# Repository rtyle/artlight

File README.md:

# artlight
This repository supports similar applications that artfully animate light.

Currently, there is a cornhole, wall clock, nixie tube clock and golden clock application supported by this repository.

Golden clock (LED sunflower): https://youtu.be/tHdfZooGRxo

Nixie tube clock: https://youtu.be/5ZdNDDC60QM

Wall clock: https://youtu.be/0ISKXnE9frU

## Parts

### Golden Clock Parts

* [5V 20W power supply](https://www.digikey.com/en/products/detail/cui-inc/SWI25-5-N-P5/7070092)
* [TinyPICO ESP32 development board](https://www.adafruit.com/product/4335)
* SMD 0.1" pin headers for mounting TinyPICO to TinyPICO IO PCB
* 2 position JST PH connection header (bundled in TinyPICO ESP32 development board package) for +5V TinyPICO power
* [3 position JST SH connection header](https://www.digikey.com/en/products/detail/jst-sales-america-inc/SM03B-SRSS-TB(LF)(SN)/926874) for LED SPI signals
* [4 position JST SH connection header](https://www.digikey.com/en/products/detail/sparkfun-electronics/PRT-14417/7652746) for I2C interface with light sensor
* 1024 [SK9822 5050 LEDs](https://www.amazon.com/gp/product/B07QXJSNLN)
* [Barrel connector jack](https://www.digikey.com/product-detail/en/cui-devices/PJ-036AH-SMT-TR/CP-036AHPJCT-ND/1530994) for +5V LED power
* [3 position 0.1" horizontal connection header](https://www.digikey.com/en/products/detail/harwin-inc/M20-8890345/6565716) for LED SPI signals
* [TSL2591 light sensor](https://www.digikey.com/en/products/detail/adafruit-industries-llc/1980/4990786)
* Appropriate cables and connectors for wiring harness
* [12" interior picture frame](https://www.etsy.com/listing/943351523/round-craft-frame-hump-profile-1-14)

### Nixie Tube Clock Parts

* [Bill of Materials](https://github.com/rtyle/artlight/blob/master/easyeda/projects/nixie/bom.csv), plus...
* [AC to 12V DC 1A wall mount power adapter](https://www.digikey.com/product-detail/en/cui-inc/SWI10-12-N-P5/102-4138-ND/6618698)
* 2 [Harwin 15 pin 2.54mm pitch](https://www.mouser.com/ProductDetail/855-M20-8771546) for SMT mount of Huzzah32 board
* 44 [Harwin H3161-05](https://www.digikey.com/product-detail/en/harwin-inc/H3161-05/952-2204-ND/3728169) sockets for nixie tube pins

Optional off-board ambient light sensor for automatic dimming
* [TSL2591 high dynamic range digital light sensor](https://www.adafruit.com/product/1980)
* [SparkFun Qwiic adapter](https://www.sparkfun.com/products/14495) TSL2591 qwiic mount
* 4 [Jumper SSH-003T-P0.2-H X2 12"](https://www.digikey.com/product-detail/en/jst-sales-america-inc/ASSHSSH28K305/455-3077-ND/6009453) TSL2591 qwiic cable
* 2 [Connector housing SH 4pos 1mm white](https://www.digikey.com/product-detail/en/jst-sales-america-inc/SHR-04V-S/455-1394-ND/759883) TSL2591 qwiic connectors

Optional on-board motion sensor plugin module for automatic on/off control
* [PIR detector I2C module](https://www.holtek.com/productdetail/-/vg/7M21x6)
* [Preci-Dip 851-87-006-10-001101 PCB connector](https://www.digikey.com/product-detail/en/preci-dip/851-87-006-10-001101/1212-1350-ND/3757600) PIR I2C mount

Optional base (something is required)
* 1 foot [Cast acrylic tubing 2.000" OD x .250" wall thickness](), cut into 9/16" slices. Four used as pedestals under PCB's nixie tubes.

### Cornhole and Wall Clock Parts

#### Cornhole and Wall Clock Common Parts

* [ESP32 board](https://www.adafruit.com/product/3405)
* [TSL2561 digital luminosity sensor breakout](https://www.adafruit.com/product/439)
* [DotStar digital LED strips](https://www.adafruit.com/product/2241)
* [2.1mm DC barrel jack (through hole)](https://www.adafruit.com/product/373)
* [Wi-Fi range extender (optional)](https://www.amazon.com/gp/product/B072MH1434)

#### Wall Clock Specific Parts

Additional parts for the clock application are
* [40 inch metal wall art](https://www.etsy.com/listing/614388701/round-metal-wall-art-perfect)
* [Custom PCB board for microprocessor](https://github.com/rtyle/artlight/blob/master/eagle/projects/artlight/artlight.brd)
* [Custom PCB board for 12 o'clock ray](https://github.com/rtyle/artlight/blob/master/eagle/projects/ray/ray0.brd)
* [Custom PCB board for other rays](https://github.com/rtyle/artlight/blob/master/eagle/projects/ray/ray.brd)
* [Mounting tape](https://www.amazon.com/gp/product/B00PKI7IBG)
* [Power supply](https://www.adafruit.com/product/1466)
* [Power Y splitter](https://www.amazon.com/gp/product/B06Y5GP7SF)
* [2.1mm DC barrel jack (surface mount)](https://www.sparkfun.com/products/12748)

#### Cornhole Specific Parts

Additional parts for the cornhole application are
* Cornhole board
* [Custom PCB board](https://github.com/rtyle/artlight/blob/master/eagle/projects/artlight/artlight.cornhole.brd)
* [Cornhole LED ring](https://www.amazon.com/gp/product/B01N7SRCQJ)
* [IR break beam sensor](https://www.adafruit.com/product/2168)
* [Vibration sensor](https://www.adafruit.com/product/1766)
* [On/off RGB switch](https://www.adafruit.com/product/3424)
* [Momentary RGB switch](https://www.adafruit.com/product/3423)
* [NPN bipolar transistors](https://www.adafruit.com/product/756)
* [Resistors](https://www.adafruit.com/product/2784)
* [Power bank](https://www.amazon.com/gp/product/B072MH1434)
* [Magnetic mount](https://www.amazon.com/gp/product/B01M0DUVZV)

## Construction

The PCB components were soldered on their respective boards.
When Huzzah32 is powered by USB cable, the 5V power jumper must first be removed.

### Golden Clock Construction

[LED PCB design files](https://github.com/rtyle/artlight/tree/master/easyeda/projects/golden)
and
[TinyPICO IO PCB design files](https://github.com/rtyle/artlight/tree/master/kicad/projects/golden/tinypico-io)

Solder LEDs and connectors to LED PCB.
Solder TinyPICO and connectors to TinyPICO IO PCB.
Build wire harness as necessary for mounting.

### Nixie Tube Clock Construction

[PCB design files](https://github.com/rtyle/artlight/tree/master/easyeda/projects/nixie)

For structural integrity, use a thick (>= 2.0mm) PCB.
Order PCB with a solder paste stencil.
Use the stencil to distribute solder paste for all components under the nixie tubes and solder them with a hot air gun.
Solder all other components individually, as appropriate.
Press in pin sockets and solder from the bottom.
Mount nixie tubes and place PCB on acrylic pedestals.

*WARNING*: The nixie tubes run at 170 volts.
To reduce exposure, do not plug in until tubes are mounted and PCB is placed on acrylic pedestals.

### Wall Clock Construction

[PCB design (artlight.\*) files](https://github.com/rtyle/artlight/tree/master/eagle/projects/artlight)
with
[boards for mounting LED strips on rays](https://github.com/rtyle/artlight/tree/master/eagle/projects/ray)

The microprocessor board is mounted on the back of the art with its luminosity sensor peeking through a hole drilled in the center.
Power is routed and split between the microprocessor and 12 o'clock ray boards.
SPI signals used to animate the individually addressable LEDs are cabled from the microprocessor board to the 12 o'clock board.

LED strips are mounted to the back of the wall art.
To reduce wiring complexity, the 12 rays are supported by PCBs.
12 o'clock is different so there is a special board for it.
Each ray is cut to length, an LED strip is cut to match, mounted with tape and soldered at the ends with LEDs advancing toward the center.
The ray boards are then mounted to the back of the art using more of the same tape.
Small strips are cut to bridge the arcs between ray bases, taped and soldered in place with LEDs advancing clockwise (from front!).
Starting at 12 o'clock, strips are cut and joined together with wire to skirt the perimeter of the art (clockwise, from front).
Only clock and data signals need to tunnel under the rays as 5V and GND can be tapped from the LED strip edges of adjacent rays.

### Cornhole Construction

[PCB design (artlight.cornhole.\*) files](https://github.com/rtyle/artlight/tree/master/eagle/projects/artlight)

The power bank is mounted with strong magnets under the board so that it might easily be unplugged, removed, charged, replaced and plugged back in.
Power from it may be switched on and off (with the on/off switch).
Switched power is split between the microprocessor board, the ring LED strip and the high side of the RGB LEDs in all the switches.

The R, G and B LEDs in the switches are separtely pulse-width-modulated (PWM) to mix the preferred color of each.
PWM switching is controlled indirectly through transistor circuits wired to the low side of the RGB LEDs of each switch.
The momentary switch outputs (closed to ground) are wired to the microprocessor board inputs dedicated for them.

Vibration sensors are strategically placed (for best performance) under the board.
The vibration sensor part may be changed to affect its sensitivity.
Their shared (parallel) output (closed to ground) is wired to the microprocessor board input dedicated for them.

IR break beam sensors are mounted across the cornhole ring for the best coverage (2 orthogonal pairs seems adequate).
Their shared (parallel) output (closed to ground) is wired to the microprocessor board input dedicated for them.

The LEDs that come with the cornhole LED ring are replaced with a clockwise (from the top) strip of 80 individually addressable LEDs.
Their control lines are wired to the microprocessor board output dedicated for them.
The ring is mounted under the board.
For best results, the material above the LED ring should be transparent (for example, an acrylic ring)
so that the lights under the board can be seen from above.

## Use

Applications must be provisioned on a Wi-Fi LAN.
Until this is done, they will offer their own Wi-Fi access point where they can be configured securely by a web browser (https://192.168.4.1).
The SSID and password for Wi-Fi access must be entered.
Optionally, an mDNS hostname may be given.

The reach of your Wi-Fi LAN may need to be increased to reach these devices.
This is best done by repositioning the devices and/or Wi-Fi access points.
If necessary, deploy a Wi-Fi range extender.

Once provisioned, preferences may be set for each application by pointing a web browser to the device (http://\<device\>/).
If supported, the mDNS hostname may be used to resolve the device address;
otherwise, the leased IP address will have to be resolved (perhaps manually) depending on the capabilities of the LAN's DHCP/DNS services.

The preferences page may be filled using "factory" default values or with the current values.
Changes to most will take effect immediately.
If not, then they will take effect when the form is submitted.

Preferences may be used to customize the presentation.
Brightness parameters may be set which may include use of the luminosity sensor.
The mDNS hostname of the board may be changed.
Parameters may be set in order to accurately present time in the given time zone.
Over-the-air software updates may also be performed.

## Golden Clock Use

It's "golden" because the LED layout that produces the spirals is based on the [golden ratio](https://en.wikipedia.org/wiki/Golden_ratio).

In clock mode, the length, width, curl, shape and color of each hand may be customized. During the first minute of each hour, the minute and second hands are suppressed and the hour hand is etched into a matching randomized swirling pattern.

In swirl mode, the randomized swirling pattern cycles through six different minute-long phases, each aligned to a particular set of spirals.

The number of spirals in each set are [Fibonacci numbers](https://en.wikipedia.org/wiki/Fibonacci_number) (13, 21, 34, 55, 89, 144).
The lower the number, the tighter (curlier) the spirals in the set.
Of all the Fibonacci numbers, these ones resolve best on a layout with this number of LEDs.
By default, the sets with 21, 55 and 144 spirals are used to resolve the hour, minute and second hands because they all curve the same way and most all are sufficient to resolve the units of their measure.
Unfortunately, 55 is not quite enough resolution for 60 minutes but it looks better than the spiral set of 89 because that curves the other way.
In any case, you can choose what you like.

A high quality power supply is required to power both the microcontroller and the LEDs.
It may be necessary to use separate power supplies for these.
If so, they must tolerate having their grounds tied together.

## Nixie Tube Clock Use

The bottom dot of the colon pulses at 30 beats per minute (a second on and a second off).
The top dot of the colon pulses at 31 beats per minute.
This results in pulsing dots that are in phase at the beginning of the minute.
They separate more as mid-minute is approached and come back together again as the next minute is approached.
Thus the colon is a very crude seconds display.

Dimming controls should be slid all the way to the left to disable dimming; otherwise, dimming will start to occur as it gets dark.
The further to the right the dimming control is set, the more dimming will be done.
When slid all the way to the right, the controlled element will dim to black when the room is black.

In an effort to combat [nixie tube cathode poisoning](https://www.google.com/search?q=nixie+tube+cathode+poisoning)
the clock will not display minutes during the first minute of every hour.
Instead, the normal minutes-places will cycle through digits that are not normally used there.
For hours less than 10, the tens-of-hours place will similarly cycle.
The display can also be temporarily put in a Clean mode (or other modes) until expectations are met.

## Wall Clock Use

There are no additional preferences for the clock application.

The clock will present time by animating hour, minute and second indicators using the LEDs mounted to the back of the art.
Hour and minute indicators will animate up and down the rays and across the inner arcs that connect them.
The second indicator will sweep across the perimeter.

## Cornhole Use

The cornhole "preferences" page may be used to keep score.
In fact, unless explicitly accessed through a URL with a preferences path (http://\<device\>/preferences), scoring is the only thing allowed.

Changing most preferences (including scoring) will be shared between boards that have been configured to use the same network port number.
For this to work effectively, only the two boards used in a cornhole game should share the same port number and each must be reachable from the other on the same network.

A preference may be used to control what the ring LED strip indicates:
* The score of each team
* The time
* Various animations

Regardless of what the ring indicates:

A short press of a momentary switch will increment the score of the associated team.
A long press of a momentary switch will decrement the score of the associated team while held.
While decrementing, if the other switch is down too then the score is reset to 0 (hold both to reset both to 0).

Vibration from the board will cause a short "lightning strike" animation to be presented over the existing ring indication.
A break in the ring's IR beam sensors will cause a short "fireworks" animation to be presented over the existing ring indication.

## Software Build, Deploy and Monitor

These projects were built on a Fedora Linux platform.
Your mileage may vary elsewhere.

Get artlight source code with its dependencies

    git clone http://github.com/rtyle/artlight.git
    cd artlight
    git submodule update --init --recursive
    (cd esp-idf; git apply ../time.c.patch)
  
[Create certificates](https://github.com/rtyle/artlight/blob/master/project/README.certificates.txt)

Install tools required by esp-idf in esp-idf-tools.

    IDF_TOOLS_PATH=esp-idf-tools esp-idf/install.sh

(Re)establish build environment.

    . esp-idf-export.sh

Select application (choose one).

    application=clock
    application=cornhole
    application=golden
    application=nixie

Build application.

    (cd project; ArtlightApplication=$application idf.py fullclean reconfigure build)

Grant user access to USB serial devices then **relogin** to get access.

    sudo usermod -a -G dialout $USER

Identify serial port to connected device.
For example,

    port=/dev/ttyUSB0

Prepare connected device and deploy application.

    (cd project; idf.py -p $port erase_flash erase_otadata)
    (cd project; idf.py -p $port flash)

Monitor serial output from device.

    (cd project; idf.py -p $port monitor)

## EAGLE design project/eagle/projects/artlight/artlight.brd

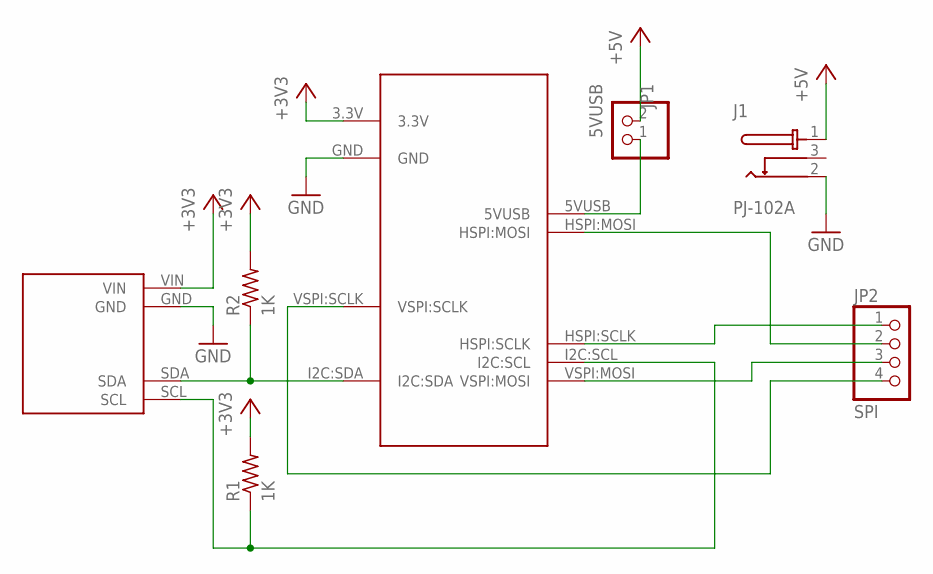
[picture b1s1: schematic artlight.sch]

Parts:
J1: PJ-102A; CUI_PJ-102A
JP1: 5VUSB; 1X02/90
JP2: SPI; 1X04/90
R1, R2: 1K; 0204/7
U$1: HUZZAH32-ARTLIGHT; FEATHERWING-ARTLIGHT
U$3: TSL2561-ARTLIGHT

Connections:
3: J1.3
5VUSB: JP1.1, U$1.5VUSB
+3V3: R1.2, R2.2, U$1.3.3V, U$3.VIN
+5V: J1.1, JP1.2
GND: J1.2, U$1.GND, U$3.GND
HSPI-MOSI: JP2.2, U$1.HSPI:MOSI
I2C-SCL: R1.1, U$1.I2C:SCL, U$3.SCL
I2C-SDA: R2.1, U$1.I2C:SDA, U$3.SDA
unnamed: JP2.3, U$1.VSPI:MOSI
unnamed: JP2.1, U$1.HSPI:SCLK
VSPI-SCLK: JP2.4, U$1.VSPI:SCLK

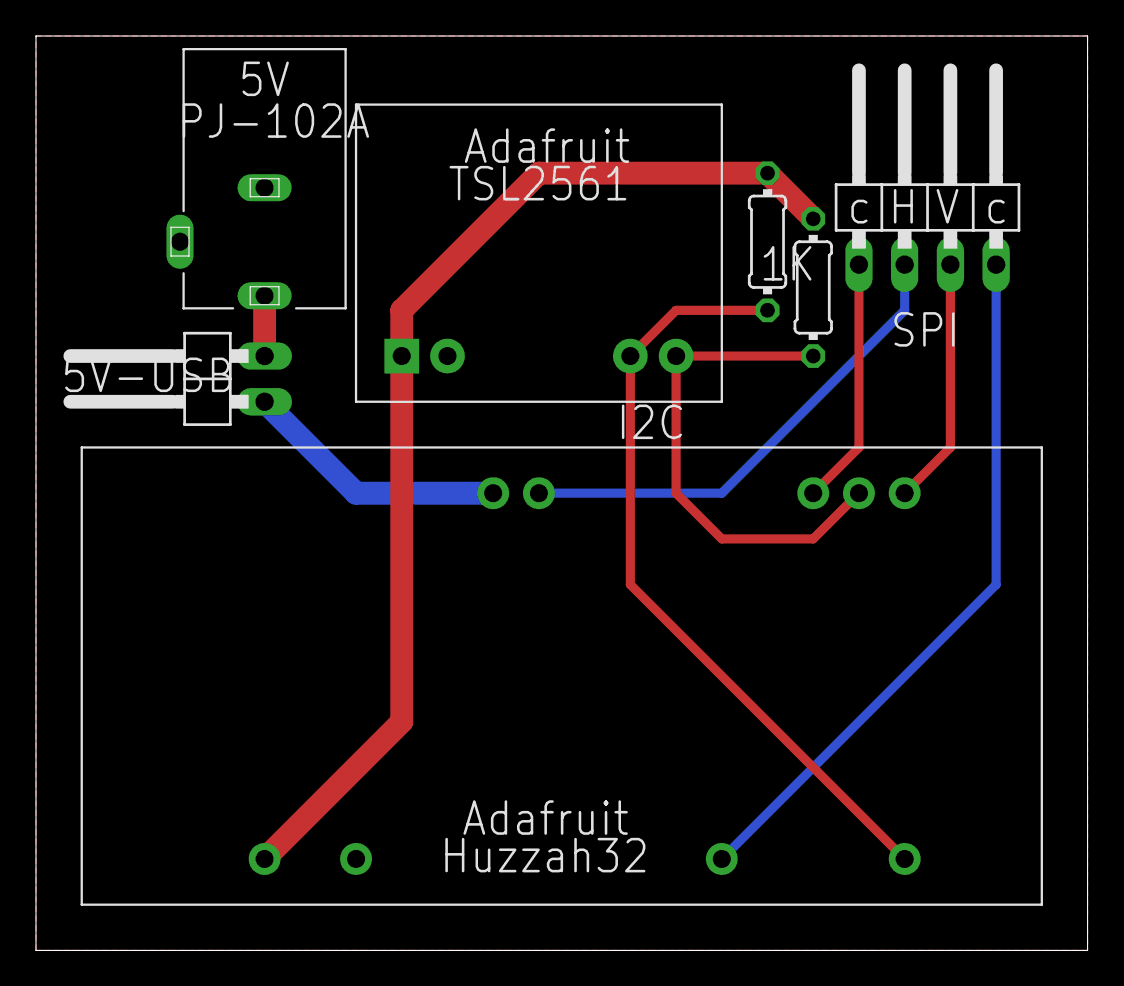
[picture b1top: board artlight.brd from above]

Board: 2 copper layers, 58.4 x 50.8 mm, 7 parts (0 on the bottom side), 10 nets.

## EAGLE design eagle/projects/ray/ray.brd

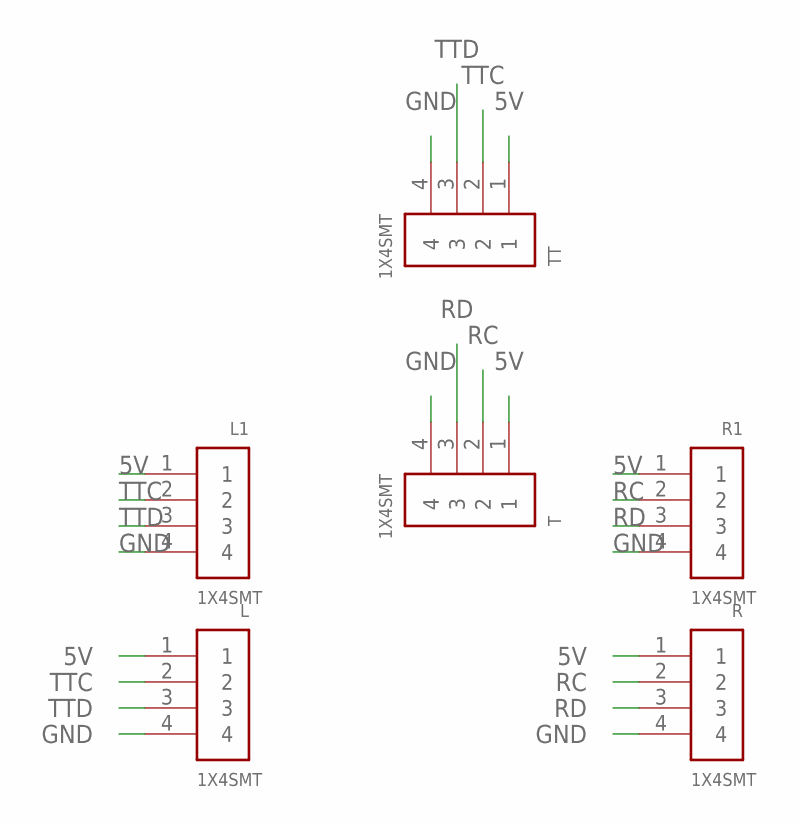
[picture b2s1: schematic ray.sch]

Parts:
L, L1: 1X4SMT; 1X4-SMT
R, R1: 1X4SMT; 1X4-SMT
T: 1X4SMT; 1X4-SMT
TT: 1X4SMT; 1X4-SMT

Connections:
5V: L.1, L1.1, R.1, R1.1, T.1, TT.1
GND: L.4, L1.4, R.4, R1.4, T.4, TT.4
RC: R.2, R1.2, T.2
RD: R.3, R1.3, T.3
TTC: L.2, L1.2, TT.2
TTD: L.3, L1.3, TT.3

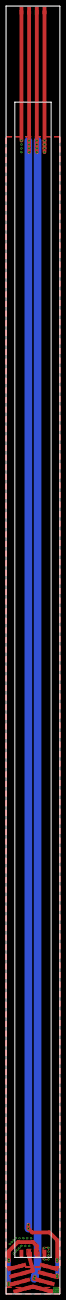
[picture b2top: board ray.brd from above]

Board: 2 copper layers, 17.8 x 425.4 mm, 6 parts (0 on the bottom side), 6 nets.

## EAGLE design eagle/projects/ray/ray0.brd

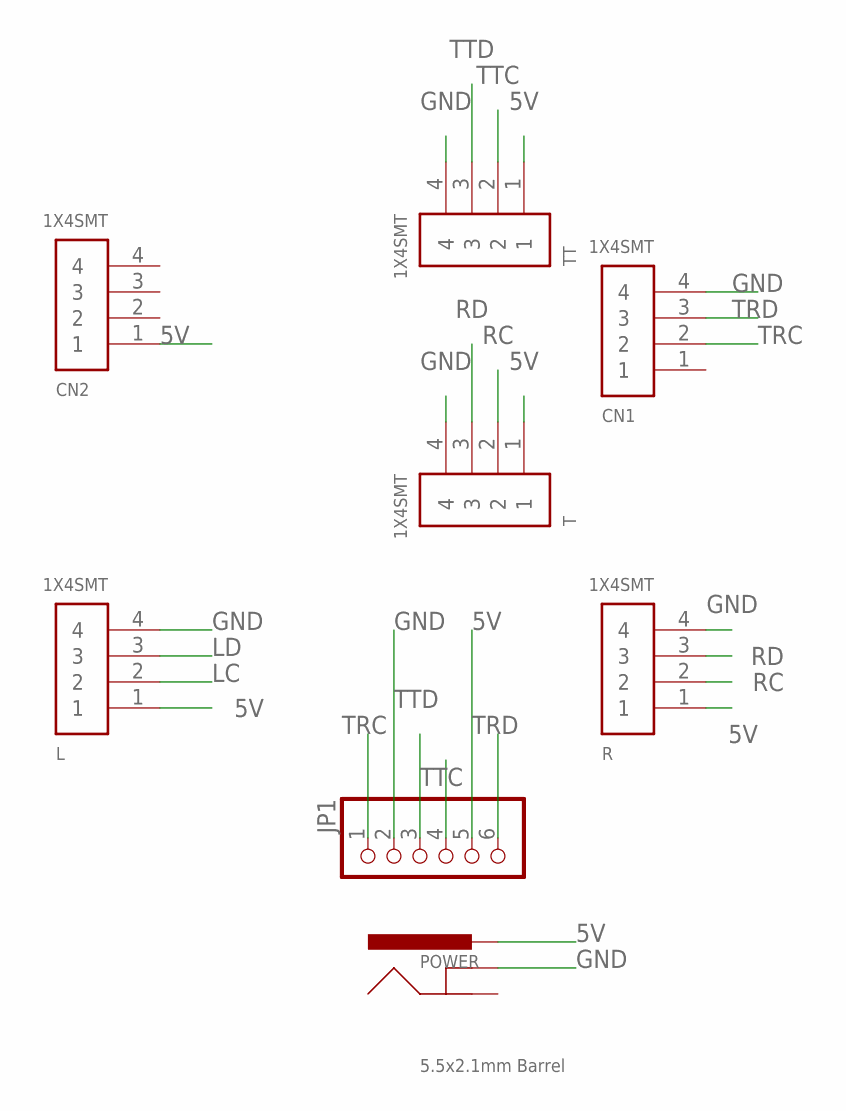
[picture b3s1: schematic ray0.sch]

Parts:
CN1, CN2: 1X4SMT; 1X4-SMT
JP1: PINHD-1X6; 1X06
L: 1X4SMT; 1X4-SMT
POWER: 5.5x2.1mm Barrel; POWER_JACK_SMD
R: 1X4SMT; 1X4-SMT
T: 1X4SMT; 1X4-SMT
TT: 1X4SMT; 1X4-SMT

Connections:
5V: CN2.1, JP1.5, L.1, POWER.VIN0 (PWR), POWER.VIN1 (PWR), R.1, T.1, TT.1
GND: CN1.4, JP1.2, L.4, POWER.GND (GNDBREAK), R.4, T.4, TT.4
LC: L.2
LD: L.3
RC: R.2, T.2
RD: R.3, T.3
TRC: CN1.2, JP1.1
TRD: CN1.3, JP1.6
TTC: JP1.4, TT.2
TTD: JP1.3, TT.3

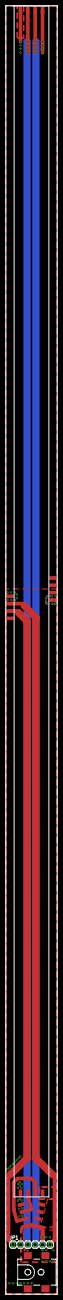
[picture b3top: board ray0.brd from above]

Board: 2 copper layers, 17.8 x 445.5 mm, 8 parts (0 on the bottom side), 8 nets.

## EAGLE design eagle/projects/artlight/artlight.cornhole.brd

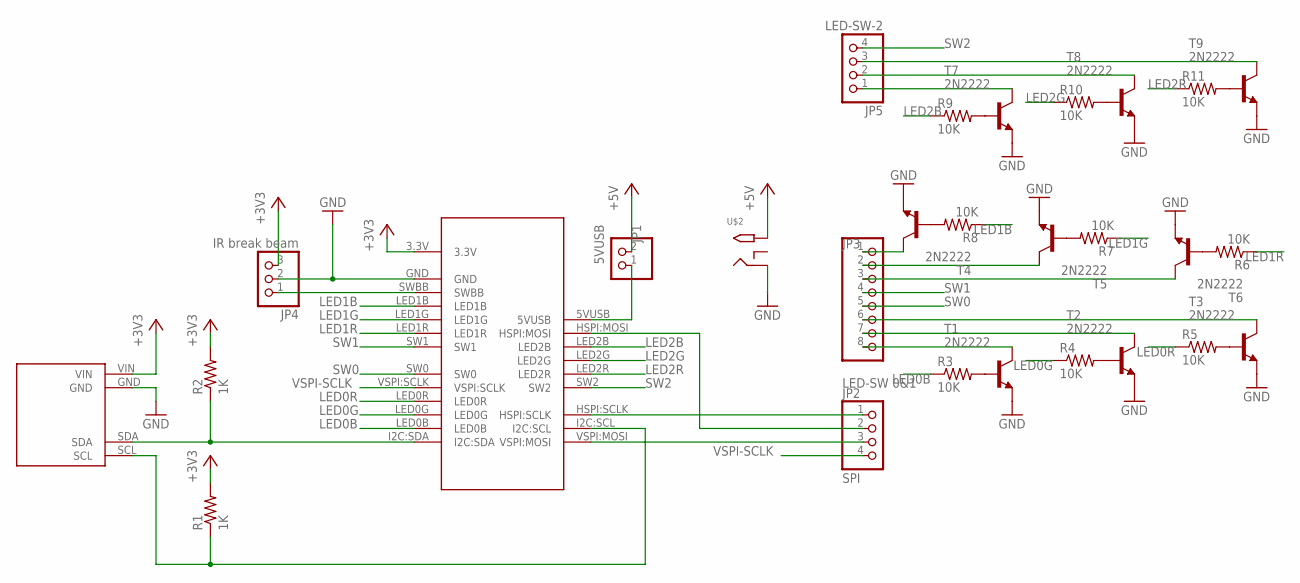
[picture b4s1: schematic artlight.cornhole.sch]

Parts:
JP1: 5VUSB; 1X02
JP2: SPI; 1X04
JP3: LED-SW 0&1; 1X08
JP4: IR break beam; 1X03
JP5: LED-SW-2; 1X04
R1, R2: 1K; 0204/7
R3, R4, R5, R6, R7, R8, R9, R10, R11: 10K; 0204V
T1, T2, T3, T4, T5, T6, T7, T8, T9: 2N2222; TO92-EBC-OVAL
U$1: HUZZAH32-ARTLIGHT.CORNHOLE; FEATHERWING-ARTLIGHT.CORNHOLE
U$2: 2.1MMJACKTHM; PJ-102A
U$3: TSL2561-ARTLIGHT

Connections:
5VUSB: JP1.1, U$1.5VUSB
+3V3: JP4.3, R1.2, R2.2, U$1.3.3V, U$3.VIN
+5V: JP1.2, U$2.TIP
GND: JP4.2, T1.E, T2.E, T3.E, T4.E, T5.E, T6.E, T7.E, T8.E, T9.E, U$1.GND, U$2.RING, U$3.GND
HSPI-MOSI: JP2.2, U$1.HSPI:MOSI
HSPI-SCLK: JP2.1, U$1.HSPI:SCLK
I2C-SCL: R1.1, U$1.I2C:SCL, U$3.SCL
I2C-SDA: R2.1, U$1.I2C:SDA, U$3.SDA
LED0B: R3.1, U$1.LED0B
LED0B-BASE: R3.2, T1.B
LED0B-PIN: JP3.8, T1.C
LED0G: R4.1, U$1.LED0G
LED0G-BASE: R4.2, T2.B
LED0G-PIN: JP3.7, T2.C
LED0R: R5.1, U$1.LED0R
LED0R-BASE: R5.2, T3.B
LED0R-PIN: JP3.6, T3.C
LED1B: R8.1, U$1.LED1B
LED1B-BASE: R8.2, T4.B
LED1B-PIN: JP3.1, T4.C
LED1G: R7.1, U$1.LED1G
LED1G-BASE: R7.2, T5.B
LED1G-PIN: JP3.2, T5.C
LED1R: R6.1, U$1.LED1R
LED1R-BASE: R6.2, T6.B
LED1R-PIN: JP3.3, T6.C
LED2B: R9.1, U$1.LED2B
LED2B-BASE: R9.2, T7.B
LED2B-PIN: JP5.1, T7.C
LED2G: R10.1, U$1.LED2G
LED2G-BASE: R10.2, T8.B
LED2G-PIN: JP5.2, T8.C
LED2R: R11.1, U$1.LED2R
LED2R-BASE: R11.2, T9.B
LED2R-PIN: JP5.3, T9.C
SW0: JP3.5, U$1.SW0
SW1: JP3.4, U$1.SW1
SW2: JP5.4, U$1.SW2
SWBB: JP4.1, U$1.SWBB
VSPI-MOSI: JP2.3, U$1.VSPI:MOSI
VSPI-SCLK: JP2.4, U$1.VSPI:SCLK

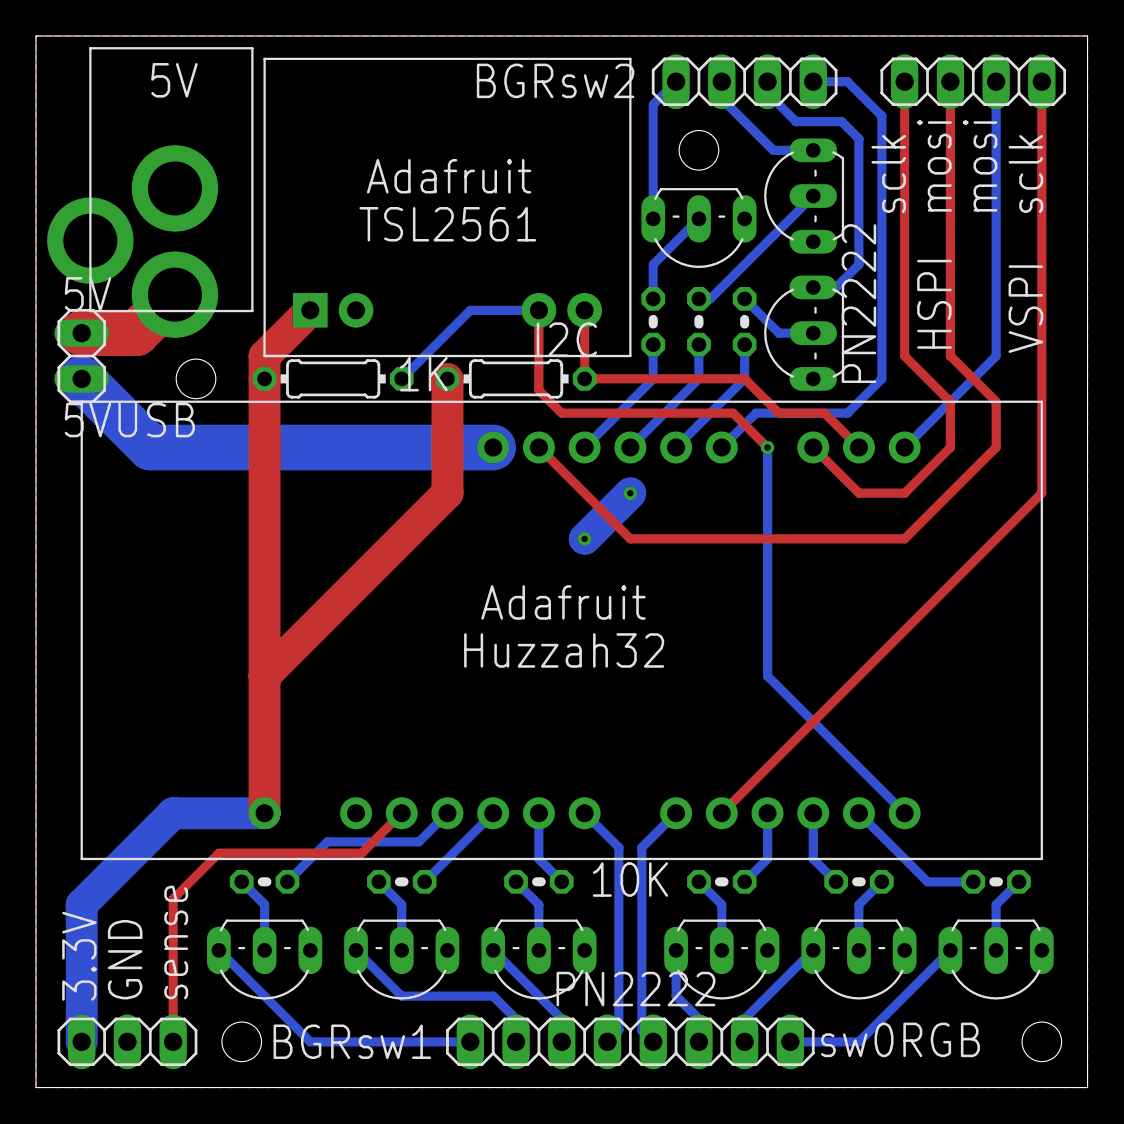
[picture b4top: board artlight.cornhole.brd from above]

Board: 2 copper layers, 58.4 x 58.4 mm, 28 parts (0 on the bottom side), 41 nets.

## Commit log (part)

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2019-02-28 move Pin observation and LED handling into Ring
2019-02-28 fix LEDC timer and channel allocation
2019-02-28 animage a and b buttons
2019-03-01 refactor
2019-03-01 led pulse with different relatively irrational frequencies
2019-03-01 refactor, comment
2019-03-02 rename
2019-03-05 Button
2019-03-07 refactor: rename
2019-03-07 Button refactor, rename, comment, tune
2019-03-08 APA102.cpp: fix toString conversion
2019-03-08 ArtTask.fadesObserver sets a ceiling on fades
2019-03-08 BellWave fixes
2019-03-09 whitespace
2019-03-09 comment
2019-03-11 preferences: {a,b,c}Shape select
2019-03-11 all ArtTask enumerated preferences handled the same way
2019-03-12 preferences: use HTML select instead of radio
2019-03-13 remove unused function.h
2019-03-13 refactor out most Ring content, place what is left in CornholeArtTask
2019-03-14 preferences: cornhole score
2019-03-14 automatically POST input numbers
2019-03-14 observe/update cornhole score
2019-03-17 emit Button held when released after hold
2019-03-17 CornholeArtTask increment/decrement score
2019-03-18 remove {a,b,c}Fades preferences - default to black
2019-03-19 display cornhole winner only
2019-03-19 for cornhole, hide all preferences except score if pathname is /
2019-03-19 fix compiler warnings
2019-03-19 optionally provision with mDNS hostname to override default/preference
2019-03-19 implement mDNS hostname preference
2019-03-20 fix ESP_ERR_NVS_NOT_FOUND error handling
2019-03-21 KeyValueBroker: support RemoteObserver(s)
2019-03-22 PeerTask sends and receives key/values to/from peers
2019-03-22 PeerTask cleanup
2019-03-22 add semi-colon line terminator after ESP_ERROR_CHECK macro
2019-03-22 esp-idf v3.2-beta3
2019-03-23 document lwip_recvmsg bug
2019-03-23 KeyValueBroker: remote -> general, publish takes fromPeer bool
2019-03-23 Cornhole::scoreObserved ignores values greater than scoreMax
2019-03-23 fix input validity check
2019-03-23 ArtTask::widthObserved: add validity check
2019-03-24 ArtTask validate dimLevel and gamma
2019-03-24 validate mDNS hostname
2019-03-24 use jquery-knob for cornhole score
2019-03-25 dynamically change {a,b}Score bgColor to {a,b}Color
2019-03-25 {a,b}Score 800x800
2019-03-25 spectrum.js
2019-03-25 remove color pattern, terminate input xml elements
2019-03-25 input type='text' class='spectrum'
2019-03-25 spectrum input elements are not just for cornhole
2019-03-26 fix knob release POST
2019-03-26 preferences.html.m4 changequote to «»
2019-03-28 preferences: make otaStart a button that submits otaUrl and starts OTA
2019-03-28 preferences: don't mess with button labels
2019-04-01 fix allocation bugs in LEDC.cpp
2019-04-02 WebSocketTask
2019-04-02 WebSocketTask close session on protocol error
2019-04-02 WebSocket::acceptSession should std::forward socket instead of std::move it
2019-04-02 KeyValueBroker::serialize(key, value)
2019-04-02 WebSocketTask sprays key value changes
2019-04-02 CONFIG_LWIP_MAX_SOCKETS=16
2019-04-04 maximize ota app partition sizes
2019-04-04 WebSocketTask: use std::move instead of std::forward, comment on shared_ptr usage
2019-04-11 Button held(int)
2019-04-11 Dial.* -> Curve.*, add lighting strikes after hole event
2019-04-12 tune lightning
2019-04-13 Bloom shape
2019-04-17 BumpCurve -> BumpsCurve
2019-04-17 BumpCurve
2019-04-17 CONFIG_TIMER_TASK_STACK_DEPTH=4096
2019-04-17 add/tune Bloom use
2019-04-17 tune Bloom
2019-04-19 https://raw.githubusercontent.com/Reputeless/PerlinNoise/master/PerlinNoise.hpp
2019-04-19 remove siv namespace from PerlinNoise
2019-04-19 PerlinNoise: double -> float
2019-04-19 mode: noise
2019-04-20 tune Perlin noise
2019-04-26 Sawtooth -> SawtoothCurve
2019-05-03 bell width is 4 sigma. calculate phase in time accurately for large time
2019-05-05 remove need for explicit PerlinNoise construction
2019-05-05 tune CornholeArtTask Spin mode
2019-05-06 CornholeArtTask Spin mode: fix wave position drift with time and changing width
2019-05-06 cleanup
2019-05-06 CornholeArtTask: pulse hour, minute and second hands on clock
2019-05-15 label auto-generated date in preferences.html as 'Version:'
2019-06-02 swap A and B (switch and LEDs)
2019-08-20 triggering a change event on a knob also triggers a release event, processing of which must be inhibited
2020-02-16 fix FoldsInRing to handle uneven folds
2020-02-17 README.md
2020-02-19 ArtLightClock.h, ClockArtTask.{h,cpp}
2020-02-19 add clock to suite of ArtLightApplication
2020-02-19 mode preference for all but score only for cornhole
2020-02-20 fix message to handle both APA102 and clone (SK9822)
2020-02-22 catch update rate too fast
2020-02-25 expose smoothTimeStepCount arg (with default and ClockArtTask override) in ArtTask constructor
2020-02-25 ClockArtTask renders to two rings: one for hours and minutes, the other for seconds
2020-03-10 add reverse checkbox input to clock preferences
2020-03-17 adjust ringSize & foldedSize to match art
2020-03-23 esp-idf v3.3.1
2020-03-29 README.md youtube link
2020-03-31 increase max indicator width from 16 to 64
2020-04-01 dialCount, ringCount, sectorCount constexpr
2020-04-01 CPP core guidelines ES.23: Prefer {} -initializer syntax
2020-04-01 sum constexpr
2020-04-02 static methods
2020-04-02 align with esp-idf v3.3.1 components/newlib/time.c
2020-04-02 fix broken time after OTA update
2020-04-28 factor out LED dial stuff from ArtTask into DialArtTask from which both ClockArtTask and CornholeArtTask now derive from
2020-04-28 ArtLightNixie skeleton
2020-05-01 TLC59711 LED driver SPI interface
2020-05-06 move SPI and I2C setup to {Clock,Cornhole,Nixie}ArtTask constructors
2020-05-17 inSecondOf not used
2020-05-17 I2C writeBytes takes const data
2020-05-17 ignoreKnobRelease only for cornhole
2020-05-24 LuxTask uses abstract LuxSensor implementation
2020-05-25 LuxSensor implementations keep track of startTime to detect underflow
2020-05-26 TSL25xx overflow only when too sensitive, underflow when not sensitive enough
2020-05-29 remove startTime from TSL2591. disable debug in TSL2561
2020-05-30 TSL2591 readLux behaves like TSL2561 until we know better
2020-05-30 add another tick to LuxTask soonAfterAvailable to eliminate occasional TSL2591 underflows
2020-06-02 LuxTask -> SensorTask, a shell task for synchronizing access to sensors
2020-06-06 incorporate TSL2591 lux equation guidance from AMS
2020-06-09 easyeda
2020-06-09 nixie clock
2020-06-10 do not repeat yourself
2020-06-12 luxBrightest
2020-07-24 add roll mode. map to nixie digits. blink colon. turn on LEDs
2020-07-25 use float powf
2020-07-25 default dots function returns 0. digitize{0,1} never returns more than 1. do not display hours 10 digit if 0. enforce minimum pwm
2020-07-25 create and use a simple PCA9685:Pwm operator that modifies itself using one unsigned value
2020-07-25 snapPwm to 0 if less than minimum value
2020-07-25 pwmFactorOf(digit)
2020-07-26 add manual clean mode and automatically clean in clock mode every hour
2020-07-27 constexpr pwmFactorFrom
2020-07-27 make sure an LED level of 1 does not turn the LED off
2020-07-27 linear dimming as a function of ambient lighting and preferences
2020-07-28 nixie dimming before brightness, no separate brightness section
2020-07-28 set nixie dimming step to 4, fade colon dots
2020-07-29 characterize nixie tube brightness in our circuit
2020-07-30 maximum LED dimming (off when pitch black) as default
2020-07-30 add nixie tube clock
2020-07-30 170 volt warning
2020-07-31 make TSL2591 I2C device optional
2020-07-31 mark optional nixie tube clock parts
2020-07-31 punctuation
2020-08-01 README links to PCB design files
2020-08-01 add Software Build, Deploy and Monitor section to README.md
2020-08-02 nixie clock motion sensor is optional. default preference update
2020-08-06 APA102::Message constructor creates encodings from default LED constructor
2020-08-06 LuxSensor::update catches all exceptions
2020-08-06 motion tooltips
2020-08-07 {initialization}
2020-08-08 set I2C clock for nixie sensor bus to 400000 (fast mode)
2020-08-10 esp_err_to_name
2020-08-11 HT7M2xxx rework
2020-08-13 avoid throw during catch
2020-08-13 Finally processing in I2C::Master::Commands desttuctor
2020-08-15 {Time,Dial,Light}Preferences
2020-08-15 pirRetrigger_(true)
2020-08-16 unneeded
2020-08-20 ESP-IDF v3.3.2, latest xtensa toolchain
2020-08-20 I2C::Master::Commands destructor checks for successful construction
2020-08-21 move sensorTask.start() to NixieArtTask::run()
2020-08-21 MotionSensor::getPeriod returns ticks
2020-08-22 not needed
2020-09-13 org.eclipse.cdt.core
2020-09-13 increase effectiveness of cathode poisoning prevention routine
2020-09-13 microsecondsSinceBootOfModeChange = get_time_since_boot()
2020-09-13 distinguish betwee decimal place index and values
2020-12-13 Pin.h disable pullups by default
2020-12-17 golden application stub on TinyPICO
2020-12-19 EasyEDA golden schematic and PCB artifacts
2020-12-19 golden.html
2020-12-20 calculate the positioning and ordering LEDs in the spiral "strip"
2020-12-30 golden.html: add parameters and links for good pre-defined combinations
2021-01-20 golden.html: numbers for c++ code
2021-01-21 GoldenArtTask: swirl
2021-01-21 GoldenArtTask: fibonacci, narrow scope
2021-01-22 GoldenArtTask: add contrast
2021-01-22 GoldenArtTask: better compile-time initialization
2021-01-23 GoldenArtTask: apply noise to radius, stretch noise with contrast
2021-01-24 GoldenArtTask: cycle through even then odd swirls
2021-01-24 GoldedArtTask: modes
2021-01-25 GoldenArtTask: Path::Iterator
2021-01-26 GoldenArtTask: clock
2021-01-26 GoldenArtTask: dim clock
2021-01-26 HalfDial
2021-01-27 HalfDial -> HalfCurve
2021-01-27 GoldenArtTask: no pulse, no scale, half indicator by direction
2021-01-28 GoldenArtTask: rename for fibonacci index
2021-01-30 SawtoothCurve::operator(): handle negative values from std::modf properly
2021-01-31 GoldenArtTask: struct Rim
2021-01-31 GoldenArtTask: index -> fibonacciIndex
2021-01-31 GoldenArtTask: rimEnd, rimName, rimDecl macros
2021-01-31 GoldenArtTask: wavePhase same for all dials, fix seam, break period for secondsDial
2021-02-01 GoldenArtTask: adjust wavePosition only for odd rimSizes
2021-02-01 GoldenArtTask: dial edge always full on
2021-02-01 GoldenArtTask: better name, reduce scope
2021-02-03 golden.html: tune rims
2021-02-03 GoldenArtTask: swirls based only on needed rims in cycle, get rid of rest
2021-02-03 golden.html: fix inconsistencies
2021-02-03 GoldenArtTask: change rim[] common_type to Array<Rim const>
2021-02-04 Array.h
2021-02-04 Update Array.h
    comment
2021-02-04 golden: add curl and length preferences
2021-02-05 GoldenArtTask: normalize width
2021-02-06 GoldenArtTask: compose rendering with int16_t precision, apply gamma correction, then encode
2021-02-06 golden brightness preference UI
2021-02-06 reduce scope
2021-02-06 GoldenArtTask: comment, name constants
2021-02-06 golden: add lux sensor with brightness/dimming controls
2021-02-07 GoldenArtTask: do not gamma correct zero
2021-02-07 golden: make sure color dimming & gamma correction do not lose non-zero rgb parts
2021-02-07 GoldenArtTask: etch hour hand into swirl background at top of hour
2021-02-09 golden: I2C pins 21 & 22
2021-02-09 golden: kicad tinypico-io board
2021-02-13 refresh snapeda downloads to originals and write-protect
2021-02-13 golden tinypico-io schematic update to use private modified symbols to pass ERC
2021-02-16 kicad grabcad library
2021-02-16 golden tinypico-io version 1.0.0
2021-02-16 golden tinypico-io footprint fixes
2021-02-16 golden tinypico-io footprint fixes, new gerbers
2021-02-25 change DialPreferences defaults, GoldenArtTask gamma
2021-03-23 Update README.md for "golden" application
2021-05-05 include esp-idf files in double quotes
2021-05-06 LEDC.* compatible with ESP_IDF_VERSION >= ESP_IDF_VERSION_VAL(4, 0, 0)
2021-05-06 include esp-idf files in double quotes, GCC diagnostic ignored "-Wimplicit-fallthrough"
2021-05-06 include esp-idf files in double quotes, address compiler warnings
2021-05-06 #pragma GCC diagnostic ignored "-Wimplicit-fallthrough, WIFI_IF_STA (not ESP_IF_WIFI_STA)
2021-05-06 #include "esp_sntp.h"
2021-05-08 #if __has_include ("esp_idf_version.h") // >= 4
2021-05-14 isDown() const, braced initializers, now{esp_timer_get_time}

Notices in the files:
parts and their libraries:
SparkFun-Connectors: Licensing: Creative Commons ShareAlike 4.0 International - https://creativecommons.org/licenses/by-sa/4.0
